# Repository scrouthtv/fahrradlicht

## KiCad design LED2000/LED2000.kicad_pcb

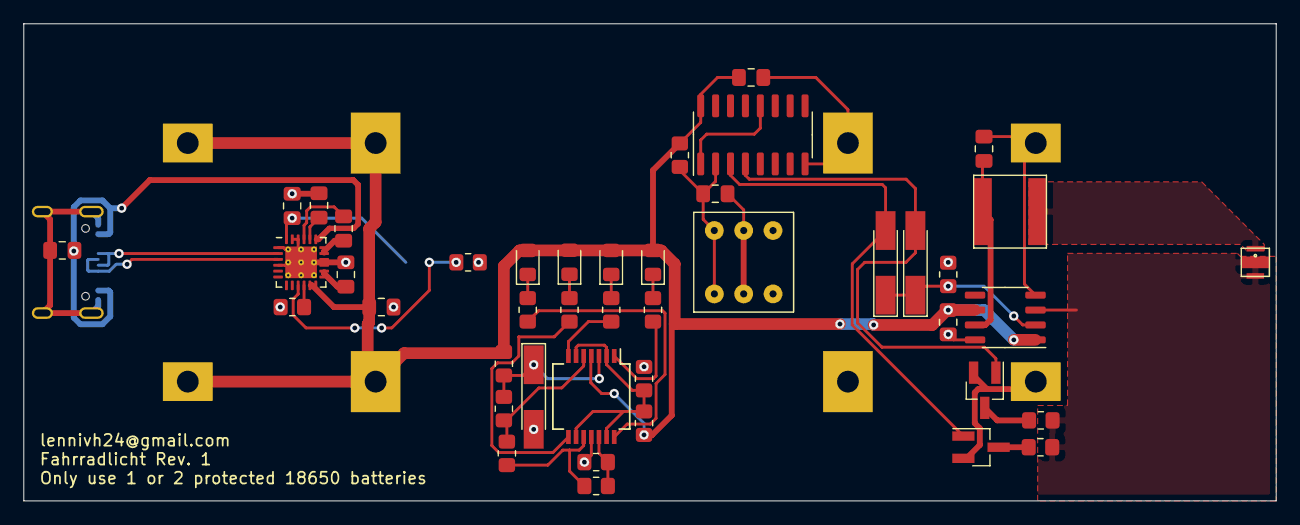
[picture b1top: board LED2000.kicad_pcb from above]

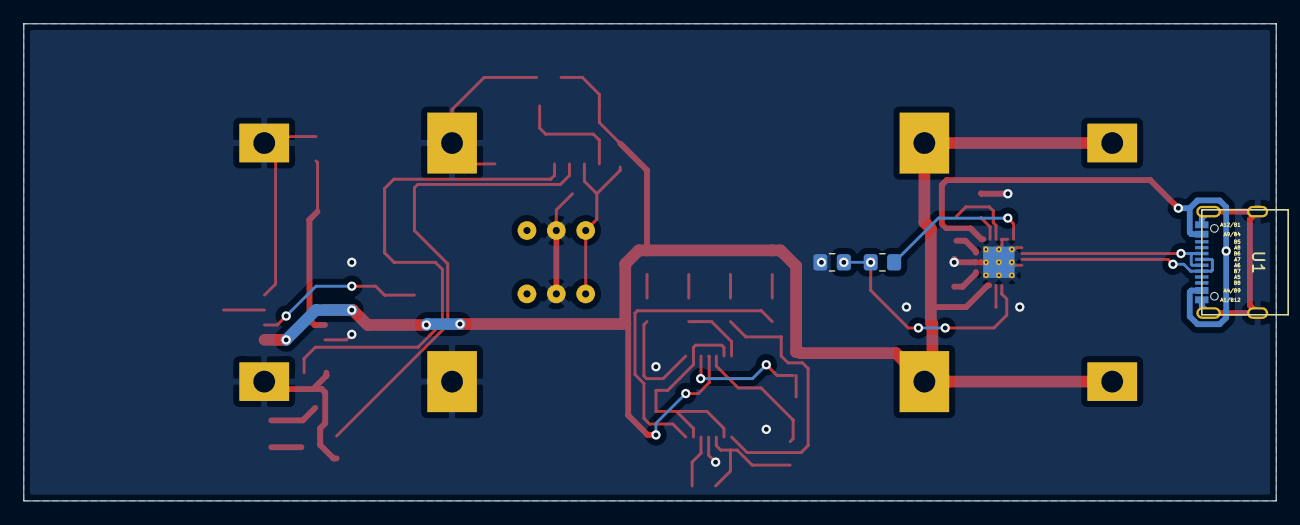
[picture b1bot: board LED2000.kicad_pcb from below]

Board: 2 copper layers, 106.7 x 40.6 mm, 48 parts (5 on the bottom side), 35 nets.

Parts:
C1, C9, C10: 1 uF; C_0805_2012Metric_Pad1.18x1.45mm_HandSolder
C2, C3, C4: 4.7 uF; C_0805_2012Metric_Pad1.18x1.45mm_HandSolder
C5, C6: 100n; C_0805_2012Metric_Pad1.18x1.45mm_HandSolder
C7: 33 nF; C_0805_2012Metric_Pad1.18x1.45mm_HandSolder
C8: 22 uF; C_0805_2012Metric_Pad1.18x1.45mm_HandSolder
D1, D2: 1N4148; D_MiniMELF_Handsoldering
D3: LED; Osram GW PLLRA1
D4: 2V4; D_MiniMELF_Handsoldering
D5, D6, D7, D8: LED; LED_0805_2012Metric_Pad1.15x1.40mm_HandSolder
J1, J2: Conn_01x02; PushIn18650
L1: L; 242408FPS
R1, R3, R15: R; R_0805_2012Metric_Pad1.20x1.40mm_HandSolder
R2, R8, R10: 10 k; R_0805_2012Metric_Pad1.20x1.40mm_HandSolder
R4, R5, R6, R7: 1 k; R_0805_2012Metric_Pad1.20x1.40mm_HandSolder
R9: 6k8; R_0805_2012Metric_Pad1.20x1.40mm_HandSolder
R11, R12, R13, R14, R16: 100; R_0805_2012Metric_Pad1.20x1.40mm_HandSolder
Rs1: 330 m; R_0805_2012Metric_Pad1.20x1.40mm_HandSolder
Rs2: 220 m; R_0805_2012Metric_Pad1.20x1.40mm_HandSolder
SW1: SW_DPDT_x2; MHPS2283V
TH1: NTC; R_0805_2012Metric_Pad1.20x1.40mm_HandSolder
U1: USB_C_12pin; USB4105
U2: LED2000; SO-8_3.9x4.9mm_P1.27mm
U3, U4: DMN3731U; SOT-23_Handsoldering
U5: 74LS163; SOIC-16_3.9x9.9mm_P1.27mm
U6: Opamp_Quad_Generic; SSOP-14_5.3x6.2mm_P0.65mm
U7: BQ24253; Texas_S-PWQFN-N24_EP2.7x2.7mm_ThermalVias

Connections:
+3V8: C3.1, C6.2, C9.2, D5.2, D6.2, D7.2, D8.2, J1.1, J2.1, R3.2, R4.1, R9.2, U2.1, U2.6, U5.16, U6.4, U7.11, U7.12
GND: C1.1, C2.1, C3.2, C4.1, C5.1, C6.1, C8.2, C9.1, C10.1, D4.2, J1.2, J2.2, R2.2, R8.1, R10.1, R15.2, R16.1, SW1.2, SW1.5, TH1.2, U1.0, U1.A1/B12, U1.A12/B1, U2.4, U2.8, U3.2, U4.2, U5.8, U6.11, U7.1, U7.4, U7.15, U7.16, U7.22, U7.23, U7.25
unnamed: C1.2, U7.20
unnamed: C2.2, U1.A4/B9, U1.A9/B4, U7.19
unnamed: C4.2, L1.1, U2.7
unnamed: C5.2, R3.1, SW1.1, SW1.4, U5.2
unnamed: C7.1, U7.17, U7.18
unnamed: C7.2, U7.21
unnamed: C8.1, U7.13, U7.14
unnamed: C10.2, R1.1, U7.24
unnamed: D1.1, D2.1, R2.1, U2.2
unnamed: D1.2, U3.1, U5.3
unnamed: D2.2, U4.1, U5.4
unnamed: D3.1, Rs1.1, Rs2.1, U2.3
unnamed: D3.2, L1.2
unnamed: D4.1, R4.2, R5.2, U6.3
unnamed: D5.1, R11.1
unnamed: D6.1, R12.1
unnamed: D7.1, R13.1
unnamed: D8.1, R14.1
unnamed: R1.2, R15.1, TH1.1, U7.9
unnamed: R5.1, R6.2, U6.5
unnamed: R6.1, R7.2, U6.10
unnamed: R7.1, R8.2, U6.12
unnamed: R9.1, R10.2, U6.2, U6.6, U6.9, U6.13
unnamed: R11.2, U6.1
unnamed: R12.2, U6.7
unnamed: R13.2, U6.8
unnamed: R14.2, U6.14
unnamed: R16.2, U7.10
unnamed: Rs1.2, U3.3
unnamed: Rs2.2, U4.3
unnamed: U1.A6, U1.B6, U7.2
unnamed: U1.A7, U1.B7, U7.3
unnamed: U5.1, U5.12

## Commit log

2022-01-10 schematic first version
2022-01-10 what is still todo
